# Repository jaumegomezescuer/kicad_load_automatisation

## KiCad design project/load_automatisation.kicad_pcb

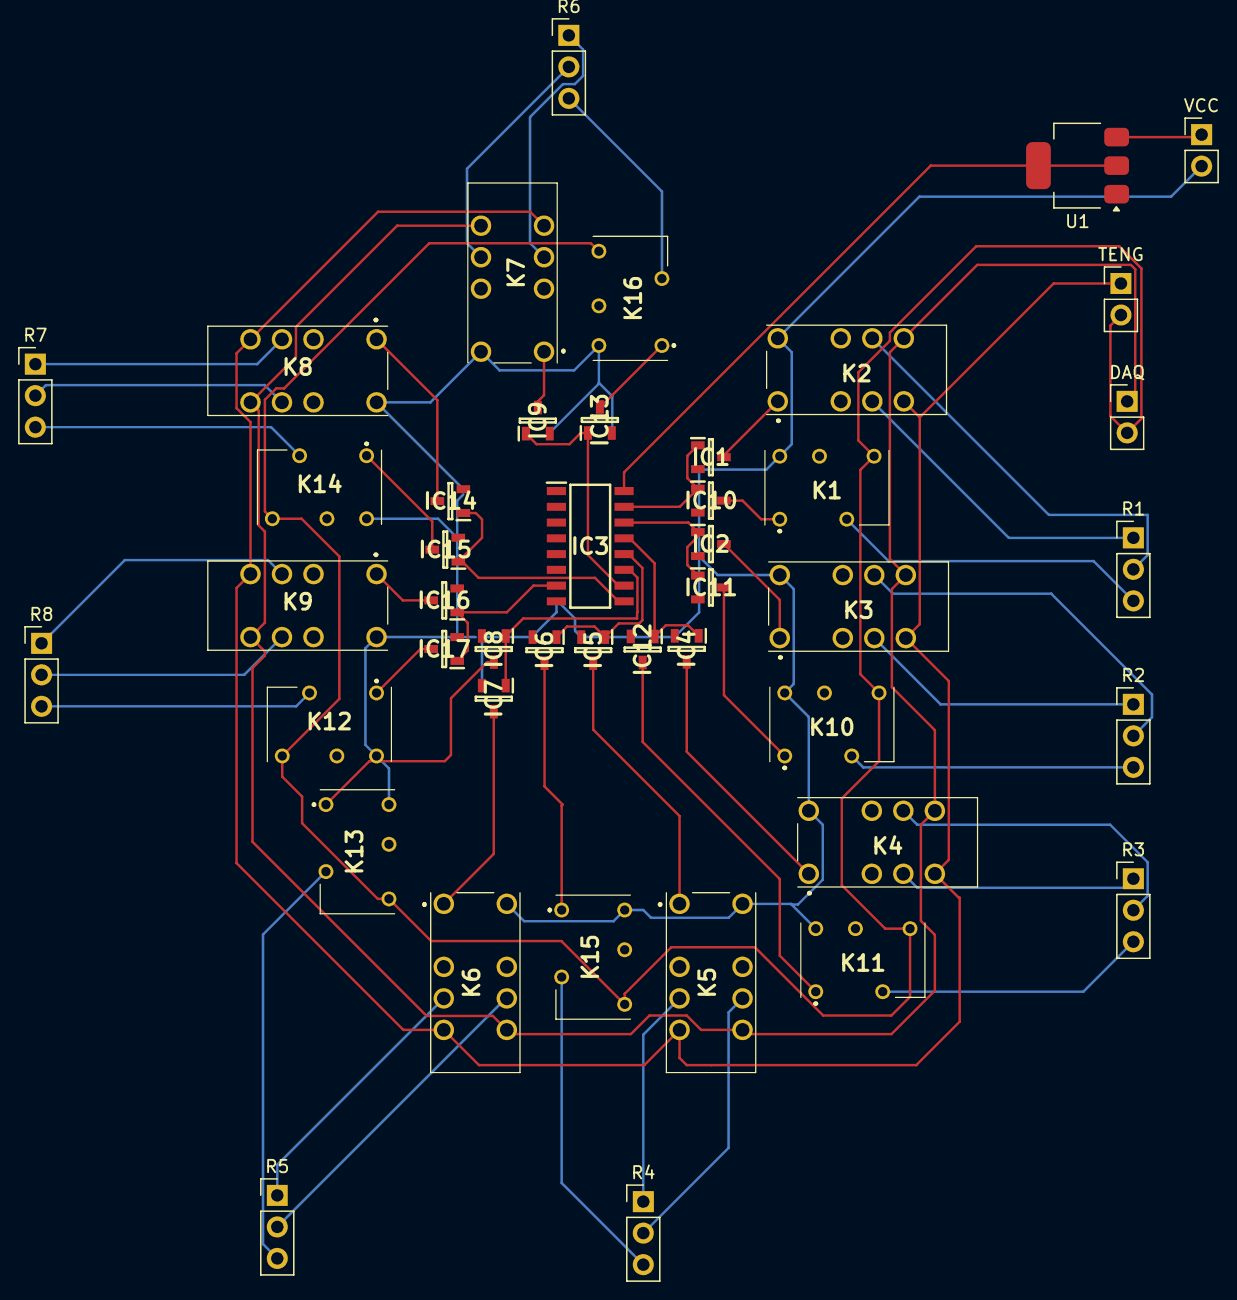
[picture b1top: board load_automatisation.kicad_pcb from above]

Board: 2 copper layers, 45 parts (0 on the bottom side), 54 nets.

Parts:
DAQ: PinHeader_1x02_P2.54mm_Vertical
IC1, IC2, IC4, IC5, IC6, IC7, IC8, IC9, IC10, IC11, IC12, IC13, IC14, IC15, IC16, IC17: DRDC3105F-7; SOT96P240X110-3N
IC3: MC74VHC138DR2G; SOIC127P600X175-16N
K1, K10, K11, K12, K13, K14, K15, K16: IMC03TS
K2, K3, K4, K5, K6, K7, K8, K9: V23079C1103B301; V23079A1001B301
R1, R2, R3, R4, R5, R6, R7, R8: PinHeader_1x03_P2.54mm_Vertical
TENG: PinHeader_1x02_P2.54mm_Vertical
U1: AMS1117-5.0; SOT-223-3_TabPin2
VCC: PinHeader_1x02_P2.54mm_Vertical

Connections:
+5V: IC3.16 (VCC), U1.2 (VO)
DAQ +: DAQ.1, K2.8 (NO_2), K3.8 (NO_2), K4.8 (NO_2), K5.8 (NO_2), K6.8 (NO_2), K7.8 (NO_2), K8.8 (NO_2), K9.8 (NO_2)
DAQ -: DAQ.2, K1.5 (NO), K10.5 (NO), K11.5 (NO), K12.5 (NO), K13.5 (NO), K14.5 (NO), K15.5 (NO), K16.5 (NO), TENG.2
GND: IC1.2 (GND), IC2.2 (GND), IC3.8 (GND), IC4.2 (GND), IC5.2 (GND), IC6.2 (GND), IC7.2 (GND), IC8.2 (GND), IC9.2 (GND), IC10.2 (GND), IC11.2 (GND), IC12.2 (GND), IC13.2 (GND), IC14.2 (GND), IC15.2 (GND), IC16.2 (GND), IC17.2 (GND), K1.8 (-), K2.12 (RESET_+/SET_-), K3.12 (RESET_+/SET_-), K4.12 (RESET_+/SET_-), K5.12 (RESET_+/SET_-), K6.12 (RESET_+/SET_-), K7.12 (RESET_+/SET_-), K8.12 (RESET_+/SET_-), K9.12 (RESET_+/SET_-), K10.8 (-), K11.8 (-), K12.8 (-), K13.8 (-), K14.8 (-), K15.8 (-), K16.8 (-), U1.1 (GND), VCC.2
Ra_1: K2.4 (COM_1), R1.1
Ra_2: K3.4 (COM_1), R2.1
Ra_3: K4.4 (COM_1), R3.1
Ra_4: K5.4 (COM_1), R4.1
Ra_5: K6.4 (COM_1), R5.1
Ra_6: K7.4 (COM_1), R6.1
Ra_7: K8.4 (COM_1), R7.1
Ra_8: K9.4 (COM_1), R8.1
Rb_1: K2.9 (COM_2), R1.2
Rb_2: K3.9 (COM_2), R2.2
Rb_3: K4.9 (COM_2), R3.2
Rb_4: K5.9 (COM_2), R4.2
Rb_5: K6.9 (COM_2), R5.2
Rb_6: K7.9 (COM_2), R6.2
Rb_7: K8.9 (COM_2), R7.2
Rb_8: K9.9 (COM_2), R8.2
Rc_1: K1.3 (COM), R1.3
Rc_2: K10.3 (COM), R2.3
Rc_3: K11.3 (COM), R3.3
Rc_4: K15.3 (COM), R4.3
Rc_5: K13.3 (COM), R5.3
Rc_6: K16.3 (COM), R6.3
Rc_7: K14.3 (COM), R7.3
Rc_8: K12.3 (COM), R8.3
TENG +: K2.5 (NO_1), K3.5 (NO_1), K4.5 (NO_1), K5.5 (NO_1), K6.5 (NO_1), K7.5 (NO_1), K8.5 (NO_1), K9.5 (NO_1), TENG.1
VCC: U1.3 (VI), VCC.1
V_OUT_1: IC1.3 (OUT), K2.1 (RESET_-/SET_+)
V_OUT_2: IC10.3 (OUT), K1.1 (+)
V_OUT_3: IC2.3 (OUT), K3.1 (RESET_-/SET_+)
V_OUT_4: IC11.3 (OUT), K10.1 (+)
V_OUT_5: IC4.3 (OUT), K4.1 (RESET_-/SET_+)
V_OUT_6: IC12.3 (OUT), K11.1 (+)
V_OUT_7: IC5.3 (OUT), K5.1 (RESET_-/SET_+)
V_OUT_8: IC6.3 (OUT), K15.1 (+)
V_OUT_9: IC7.3 (OUT), K6.1 (RESET_-/SET_+)
V_OUT_10: IC8.3 (OUT), K13.1 (+)
V_OUT_11: IC9.3 (OUT), K7.1 (RESET_-/SET_+)
V_OUT_12: IC13.3 (OUT), K16.1 (+)
V_OUT_13: IC14.3 (OUT), K8.1 (RESET_-/SET_+)
V_OUT_14: IC15.3 (OUT), K14.1 (+)
V_OUT_15: IC16.3 (OUT), K9.1 (RESET_-/SET_+)
V_OUT_16: IC17.3 (OUT), K12.1 (+)
Y0: IC1.1 (IN), IC3.15 (~Y0), IC10.1 (IN)
Y1: IC2.1 (IN), IC3.14 (~Y1), IC11.1 (IN)
Y2: IC3.13 (~Y2), IC4.1 (IN), IC12.1 (IN)
Y3: IC3.12 (~Y3), IC5.1 (IN), IC6.1 (IN)
Y4: IC3.11 (~Y4), IC7.1 (IN), IC8.1 (IN)
Y5: IC3.10 (~Y5), IC9.1 (IN), IC13.1 (IN)
Y6: IC3.9 (~Y6), IC14.1 (IN), IC15.1 (IN)
Y7: IC3.7 (~Y7), IC16.1 (IN), IC17.1 (IN)

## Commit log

2024-10-07 first test
